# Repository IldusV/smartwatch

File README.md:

1. Download https://github.com/lvgl/lvgl library into the root directory of the smartwatch project
3. Add fb_tft display driver into linux kerner directory for GC9A01A  
4. Add CST816S touchscreen driver into the kernel directory
5. Configure Device Tree

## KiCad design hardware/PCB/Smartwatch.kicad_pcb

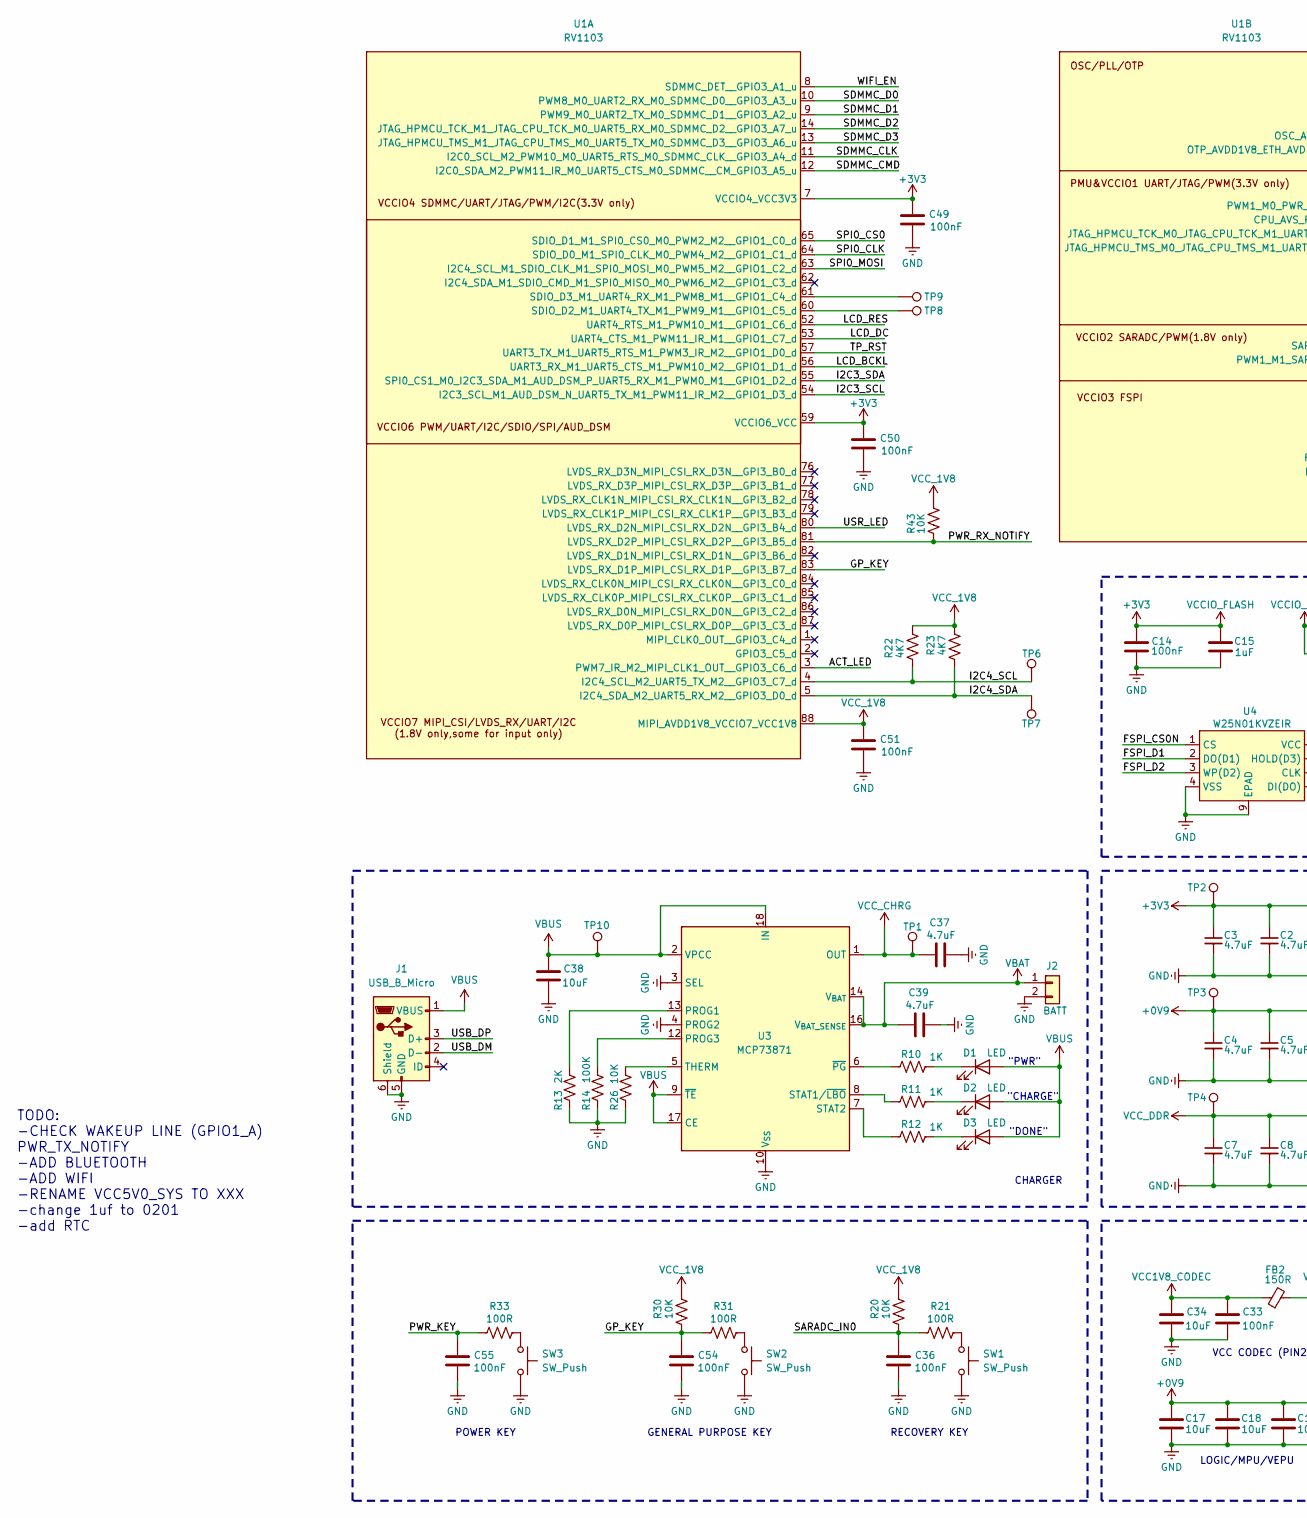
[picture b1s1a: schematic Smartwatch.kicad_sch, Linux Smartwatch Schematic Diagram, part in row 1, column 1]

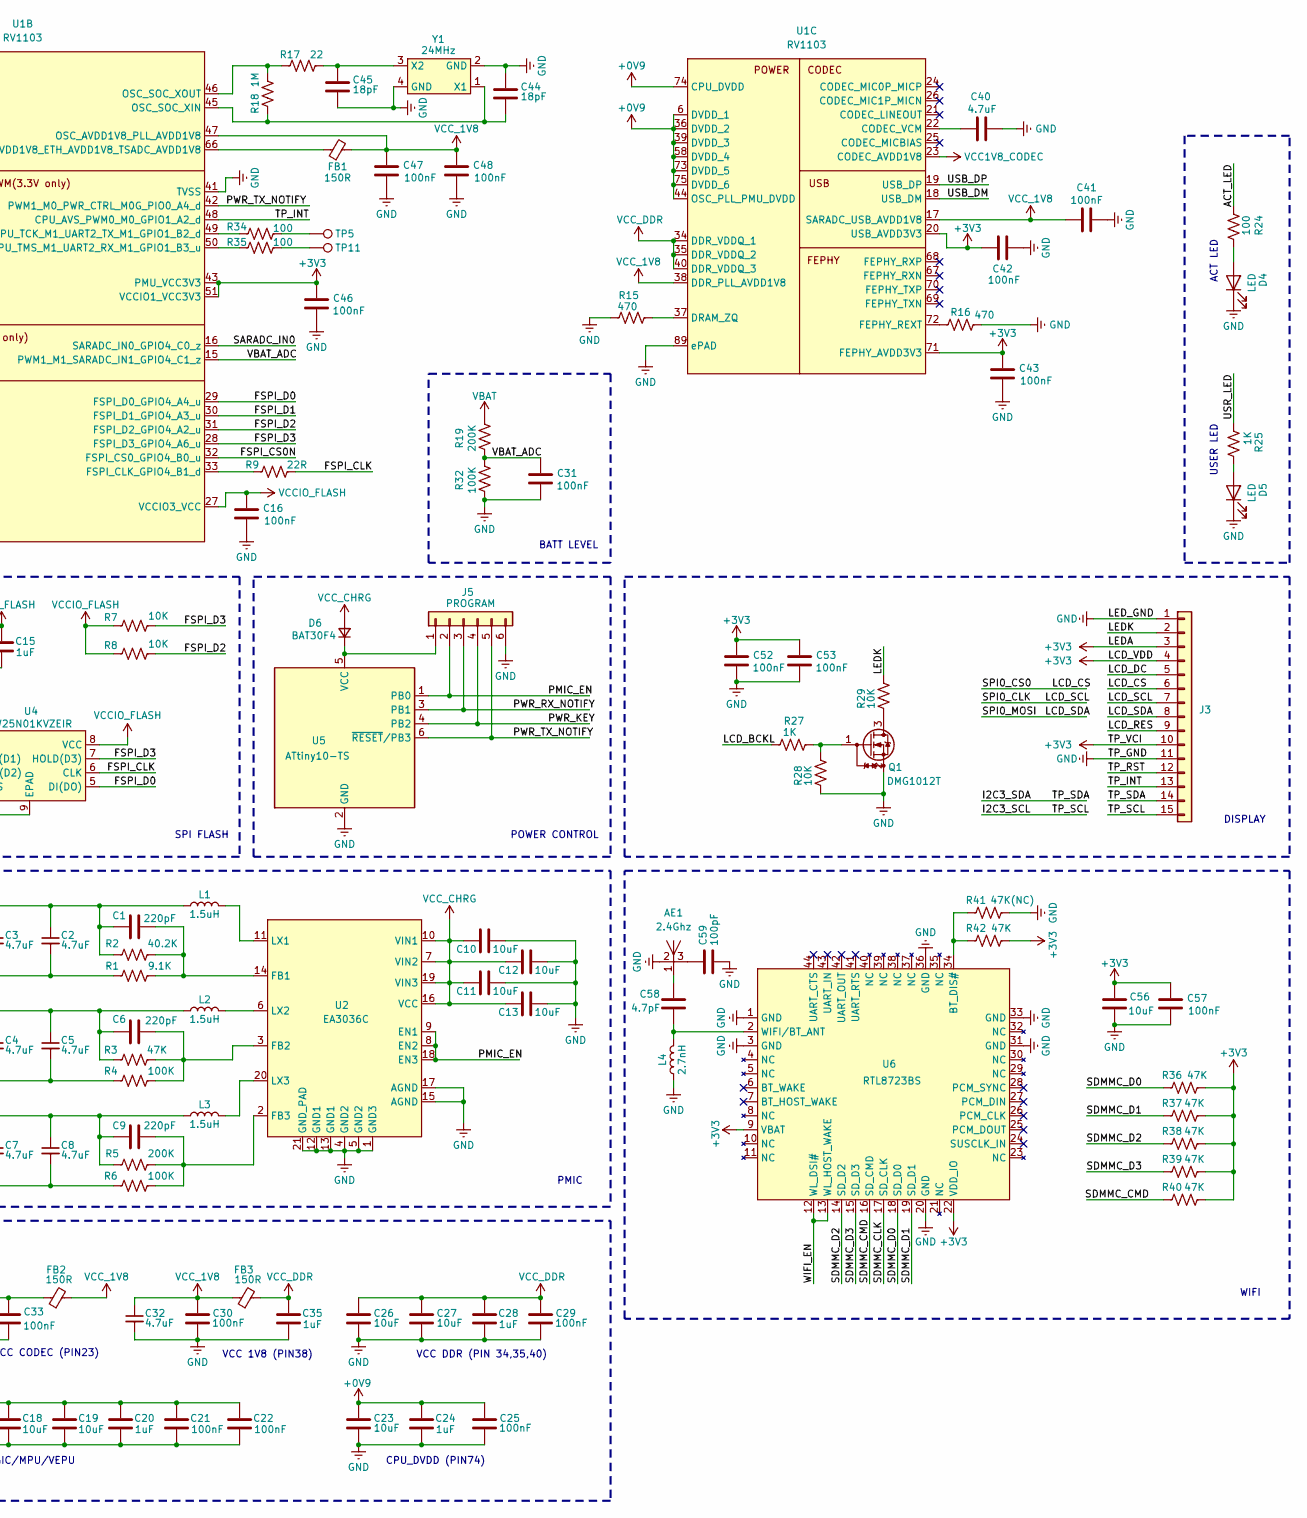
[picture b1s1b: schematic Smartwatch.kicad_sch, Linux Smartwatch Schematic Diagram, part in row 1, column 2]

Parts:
AE1: 2.4Ghz; 2.4Ghz_TE_Antenna
C1, C6, C9: 220pF; C_0201_0603Metric
C2, C3, C4, C5, C7, C8, C32, C37, C39, C40: 4.7uF; C_0201_0603Metric
C10, C11, C12, C13, C17, C18, C19, C23, C26, C27, C34, C38, C56: 10uF; C_0402_1005Metric
C14, C16, C21, C22, C25, C29, C30, C31, C33, C36, C41, C42, C43, C46, C47, C48, C49, C50, C51, C52, C53, C54, C55, C57: 100nF; C_0201_0603Metric
C15, C20, C24, C28, C35: 1uF; C_0201_0603Metric
C44, C45: 18pF; C_0201_0603Metric
C58: 4.7pF; C_0201_0603Metric
C59: 100pF; C_0201_0603Metric
D1, D2, D3, D4, D5: LED; LED_0201_0603Metric
D6: BAT30F4; D_0201_0603Metric
FB1, FB2, FB3: 150R; L_0402_1005Metric
J1: USB_B_Micro; USB_Micro-B_Molex_47346-0001
J2: BATT; JST_Aliexpress_KAN_shop_1x02-1MP_P0.80mm_Horizontal
J3: Conn_01x15; Amphenol_1x15-1MP_P0.5mm_Horizontal
J5: PROGRAM; pinpad6
L1, L2, L3: 1.5uH; L_1008_2520Metric
L4: 2.7nH; L_0402_1005Metric
Q1: DMG1012T; SOT-523
R1: 9.1K; R_0201_0603Metric
R2: 40.2K; R_0201_0603Metric
R3, R36, R37, R38, R39, R40, R42: 47K; R_0201_0603Metric
R4, R6, R14, R32: 100K; R_0201_0603Metric
R5, R19: 200K; R_0201_0603Metric
R7, R8, R20, R26, R28, R29, R30, R43: 10K; R_0201_0603Metric
R9: 22R; R_0201_0603Metric
R10, R11, R12, R25, R27: 1K; R_0201_0603Metric
R13: 2K; R_0201_0603Metric
R15, R16: 470; R_0201_0603Metric
R17: 22; R_0201_0603Metric
R18: 1M; R_0201_0603Metric
R21, R31, R33: 100R; R_0201_0603Metric
R22, R23: 4K7; R_0201_0603Metric
R24, R34, R35: 100; R_0201_0603Metric
R41: 47K(NC); R_0201_0603Metric
SW1, SW2, SW3: SW_Push; SW_1.8x4.5x3.5
TP1, TP2, TP3, TP4, TP5, TP6, TP7, TP8, TP9, TP10, TP11: TestPoint; TP
U1: RV1103; QFN-88_EP_9x9_Pitch0.35mm
U2: EA3036C; QFN-20-1EP_3x3mm_P0.4mm_EP1.65x1.65mm
U3: MCP73871; QFN-20-1EP_4x4mm_P0.5mm_EP2.5x2.5mm
U4: W25N01KVZEIR; WSON-8-1EP_8x6mm_P1.27mm_EP3.4x4.3mm
U5: ATtiny10-TS; SOT-23-6
U6: RTL8723BS; QFN-44_12.64x12.64_Pitch0.9mm
Y1: 24MHz; Crystal_SMD_2016-4Pin_2.0x1.6mm

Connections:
+0V9: C4.1, C5.1, C6.1, C17.1, C18.1, C19.1, C20.1, C21.2, C22.2, C23.1, C24.1, C25.2, L2.1, R3.1, TP3.1, U1.6 (DVDD_1), U1.36 (DVDD_2), U1.39 (DVDD_3), U1.44 (OSC_PLL_PMU_DVDD), U1.58 (DVDD_4), U1.73 (DVDD_5), U1.74 (CPU_DVDD), U1.75 (DVDD_6)
+3V3: C1.1, C2.1, C3.1, C14.2, C15.1, C16.2, C42.2, C43.2, C46.2, C49.2, C50.2, C52.2, C53.2, C56.1, C57.2, J3.3, J3.4, J3.10, L1.1, R2.1, R7.1, R8.1, R36.2, R37.2, R38.2, R39.2, R40.2, R42.2, TP2.1, U1.7 (VCCIO4_VCC3V3), U1.20 (USB_AVDD3V3), U1.27 (VCCIO3_VCC), U1.43 (PMU_VCC3V3), U1.51 (VCCIO1_VCC3V3), U1.59 (VCCIO6_VCC), U1.71 (FEPHY_AVDD3V3), U4.8 (VCC), U6.9 (VBAT), U6.22 (VDD_IO)
/ACT_LED: R24.1, U1.3 (PWM7_IR_M2_MIPI_CLK1_OUT__GPIO3_C6_d)
/FSPI_CLK: R9.2, U4.6 (CLK)
/FSPI_CS0N: U1.32 (FSPI_CS0_GPIO4_B0_u), U4.1 (CS)
/FSPI_D0: U1.29 (FSPI_D0_GPIO4_A4_u), U4.5 (DI(DO))
/FSPI_D1: U1.30 (FSPI_D1_GPIO4_A3_u), U4.2 (DO(D1))
/FSPI_D2: R8.2, U1.31 (FSPI_D2_GPIO4_A2_u), U4.3 (WP(D2))
/FSPI_D3: R7.2, U1.28 (FSPI_D3_GPIO4_A6_u), U4.7 (HOLD(D3))
/GP_KEY: C54.2, R30.1, R31.1, U1.83 (LVDS_RX_D1P_MIPI_CSI_RX_D1P__GPI3_B7_d)
/I2C3_SCL: J3.15, U1.54 (I2C3_SCL_M1_AUD_DSM_N_UART5_TX_M1_PWM11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)
/I2C3_SDA: J3.14, U1.55 (SPI0_CS1_M0_I2C3_SDA_M1_AUD_DSM_P_UART5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)
/I2C4_SCL: R22.1, TP6.1, U1.4 (I2C4_SCL_M2_UART5_TX_M2__GPIO3_C7_d)
/I2C4_SDA: R23.1, TP7.1, U1.5 (I2C4_SDA_M2_UART5_RX_M2__GPIO3_D0_d)
/LCD_BCKL: R27.1, U1.56 (UART3_RX_M1_UART5_CTS_M1_PWM10_M2__GPIO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)
/LCD_CS: J3.6, U1.65 (SDIO_D1_M1_SPI0_CS0_M0_PWM2_M2__GPIO1_C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)
/LCD_DC: J3.5, U1.53 (UART4_CTS_M1_PWM11_IR_M1__GPIO1_C7_d)
/LCD_RES: J3.9, U1.52 (UART4_RTS_M1_PWM10_M1__GPIO1_C6_d)
/LCD_SCL: J3.7, U1.64 (SDIO_D0_M1_SPI0_CLK_M0_PWM4_M2__GPIO1_C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)
/LCD_SDA: J3.8, U1.63 (I2C4_SCL_M1_SDIO_CLK_M1_SPI0_MOSI_M0_PW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)
/LEDK: J3.2, R29.2
/PMIC_EN: J5.2, U2.8 (EN2), U2.9 (EN1), U2.18 (EN3), U5.1 (PB0)
/PWR_KEY: C55.2, J5.4, R33.1, U5.4 (PB2)
/PWR_RX_NOTIFY: J5.3, R43.1, U1.81 (LVDS_RX_D2P_MIPI_CSI_RX_D2P__GPI3_B5_d), U5.3 (PB1)
/PWR_TX_NOTIFY: J5.5, U1.42 (PWM1_M0_PWR_CTRL_M0G_PIO0_A4_d), U5.6 (~RESET/PB3)
/SARADC_IN0: C36.2, R20.1, R21.1, U1.16 (SARADC_IN0_GPIO4_C0_z)
/SDMMC_CLK: U1.11 (I2C0_SCL_M2_PWM10_M0_UART5_RTS_M0_SDMMC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), U6.17 (SD_CLK)
/SDMMC_CMD: R40.1, U1.12 (I2C0_SDA_M2_PWM11_IR_M0_UART5_CTS_M0_SD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), U6.16 (SD_CMD)
/SDMMC_D0: R36.1, U1.10 (PWM8_M0_UART2_RX_M0_SDMMC_D0__GPIO3_A3_u), U6.18 (SD_D0)
/SDMMC_D1: R37.1, U1.9 (PWM9_M0_UART2_TX_M0_SDMMC_D1__GPIO3_A2_u), U6.19 (SD_D1)
/SDMMC_D2: R38.1, U1.14 (JTAG_HPMCU_TCK_M1_JTAG_CPU_TCK_M0_UART5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), U6.14 (SD_D2)
/SDMMC_D3: R39.1, U1.13 (JTAG_HPMCU_TMS_M1_JTAG_CPU_TMS_M0_UART5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), U6.15 (SD_D3)
/TP_INT: J3.13, U1.48 (CPU_AVS_PWM0_M0_GPIO1_A2_d)
/TP_RST: J3.12, U1.57 (UART3_TX_M1_UART5_RTS_M1_PWM3_IR_M2__GP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)
/USB_DM: J1.2 (D-), U1.18 (USB_DM)
/USB_DP: J1.3 (D+), U1.19 (USB_DP)
/USR_LED: R25.1, U1.80 (LVDS_RX_D2N_MIPI_CSI_RX_D2N__GPI3_B4_d)
/VBAT_ADC: C31.2, R19.1, R32.2, U1.15 (PWM1_M1_SARADC_IN1_GPIO4_C1_z)
/WIFI_EN: U1.8 (SDMMC_DET__GPIO3_A1_u), U6.12 (WL_DSI#), U6.13 (WL_HOST_WAKE)
GND: AE1.2, C2.2, C3.2, C4.2, C5.2, C7.2, C8.2, C10.1, C11.1, C12.1, C13.1, C14.1, C15.2, C16.1, C17.2, C18.2, C19.2, C20.2, C21.1, C22.1, C23.2, C24.2, C25.1, C26.2, C27.2, C28.2, C29.1, C30.1, C31.1, C32.2, C33.1, C34.2, C35.2, C36.1, C37.2, C38.2, C39.2, C40.2, C41.2, C42.1, C43.1, C44.2, C45.1, C46.1, C47.1, C48.1, C49.1, C50.1, C51.1, C52.1, C53.1, C54.1, C55.1, C56.2, C57.1, C59.2, D4.1 (K), D5.1 (K), J1.5 (GND), J1.6 (Shield), J2.2, J3.1, J3.11, J5.6, L4.1, Q1.2 (S), R1.1, R4.1, R6.1, R13.1, R14.1, R15.1, R16.2, R26.1, R28.1, R32.1, R41.2, SW1.2, SW2.2, SW3.2, U1.41 (TVSS), U1.89 (ePAD), U2.1 (GND3), U2.4 (GND2), U2.5 (GND2), U2.12 (GND1), U2.13 (GND1), U2.15 (AGND), U2.17 (AGND), U2.21 (GND_PAD), U3.3 (SEL), U3.4 (PROG2), U3.10 (V_{SS}), U3.11 (V_{SS}), U3.21 (V_{SS}), U4.4 (VSS), U4.9 (EPAD), U5.2 (GND), U6.1 (GND), U6.3 (GND), U6.20 (GND), U6.31 (GND), U6.33 (GND), U6.36 (GND), Y1.2 (GND), Y1.4 (GND)
unnamed: AE1.1, C58.2
unnamed: AE1.3, C59.1
unnamed: D1.1 (K), R10.2
unnamed: D2.1 (K), R11.2
unnamed: D3.1 (K), R12.2
unnamed: D4.2 (A), R24.2
unnamed: D5.2 (A), R25.2
unnamed: D6.1 (K), J5.1, U5.5 (VCC)
unnamed: Q1.3 (D), R29.1
unnamed: Q1.1 (G), R27.2, R28.2
unnamed: R21.2, SW1.1
unnamed: R31.2, SW2.1
unnamed: R33.2, SW3.1
unnamed: R34.2, TP5.1
unnamed: R35.2, TP11.1
unnamed: TP8.1, U1.60 (SDIO_D2_M1_UART4_TX_M1_PWM9_M1__GPIO1_C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)
unnamed: TP9.1, U1.61 (SDIO_D3_M1_UART4_RX_M1_PWM8_M1__GPIO1_C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)
unnamed: R9.1, U1.33 (FSPI_CLK_GPIO4_B1_d)
unnamed: R34.1, U1.49 (JTAG_HPMCU_TCK_M0_JTAG_CPU_TCK_M1_UART2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)
unnamed: R35.1, U1.50 (JTAG_HPMCU_TMS_M0_JTAG_CPU_TMS_M1_UART2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)
unnamed: C44.1, R18.1, U1.45 (OSC_SOC_XIN), Y1.1 (X1)
unnamed: R17.1, R18.2, U1.46 (OSC_SOC_XOUT)
unnamed: FB1.1, U1.66 (OTP_AVDD1V8_ETH_AVDD1V8_TSADC_AVDD1V8)
unnamed: C40.1, U1.22 (CODEC_VCM)
unnamed: R15.2, U1.37 (DRAM_ZQ)
unnamed: R16.1, U1.72 (FEPHY_REXT)
unnamed: C1.2, R1.2, R2.2, U2.14 (FB1)
unnamed: C6.2, R3.2, R4.2, U2.3 (FB2)
unnamed: C9.2, R5.2, R6.2, U2.2 (FB3)
unnamed: L1.2, U2.11 (LX1)
unnamed: L2.2, U2.6 (LX2)
unnamed: L3.2, U2.20 (LX3)
unnamed: R13.2, U3.13 (PROG1)
unnamed: R14.2, U3.12 (PROG3)
unnamed: R11.1, U3.8 (STAT1/~LBO)
unnamed: R12.1, U3.7 (STAT2)
unnamed: R26.2, U3.5 (THERM)
unnamed: R10.1, U3.6 (~PG)
unnamed: R41.1, R42.1, U6.34 (BT_DIS#)
unnamed: C58.1, L4.2, U6.2 (WIFI/BT_ANT)
unnamed: C45.2, R17.2, Y1.3 (X2)
VBAT: C39.1, J2.1, R19.2, U3.14 (V_{BAT}), U3.15 (V_{BAT}), U3.16 (V_{BAT_SENSE})
VBUS: C38.1, D1.2 (A), D2.2 (A), D3.2 (A), J1.1 (VBUS), TP10.1, U3.2 (VPCC), U3.9 (~TE), U3.17 (CE), U3.18 (IN), U3.19 (IN)
VCC1V8_CODEC: C33.2, C34.1, FB2.1, U1.23 (CODEC_AVDD1V8)
VCC_1V8: C30.2, C32.1, C41.1, C47.2, C48.2, C51.2, FB1.2, FB2.2, FB3.1, R20.2, R22.2, R23.2, R30.2, R43.2, U1.17 (SARADC_USB_AVDD1V8), U1.38 (DDR_PLL_AVDD1V8), U1.47 (OSC_AVDD1V8_PLL_AVDD1V8), U1.88 (MIPI_AVDD1V8_VCCIO7_VCC1V8)
VCC_CHRG: C10.2, C11.2, C12.2, C13.2, C37.1, D6.2 (A), TP1.1, U2.7 (VIN2), U2.10 (VIN1), U2.16 (VCC), U2.19 (VIN3), U3.1 (OUT), U3.20 (OUT)
VCC_DDR: C7.1, C8.1, C9.1, C26.1, C27.1, C28.1, C29.2, C35.1, FB3.2, L3.1, R5.1, TP4.1, U1.34 (DDR_VDDQ_1), U1.35 (DDR_VDDQ_2), U1.40 (DDR_VDDQ_3)

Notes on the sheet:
"DONE"
POWER CONTROL
LOGIC/MPU/VEPU
ACT LED
"PWR"
GENERAL PURPOSE KEY
CPU_DVDD (PIN74)
VCC CODEC (PIN23)
"CHARGE"
RECOVERY KEY
WIFI
CHARGER
SPI FLASH
BATT LEVEL
DISPLAY
USER LED
VCC DDR (PIN 34,35,40)
PMIC
TODO: -CHECK WAKEUP LINE (GPIO1_A) PWR_TX_NOTIFY -ADD BLUETOOTH -ADD WIFI -RENAME VCC5V0_SYS TO XXX -change 1uf to 0201 -add RTC
VCC 1V8 (PIN38)
POWER KEY

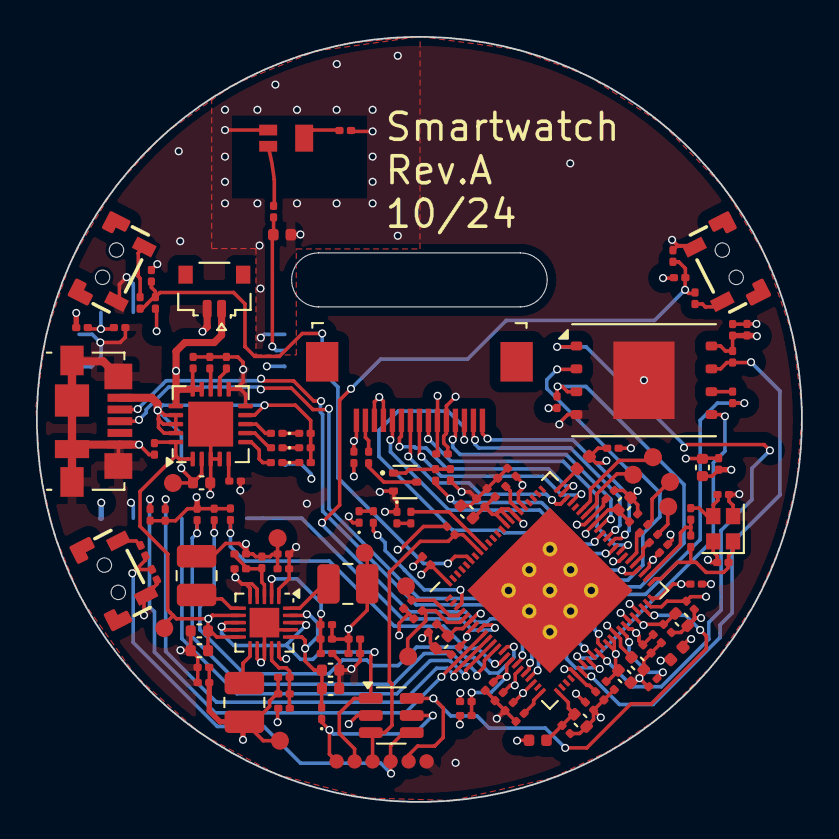
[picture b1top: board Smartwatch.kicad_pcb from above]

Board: 4 copper layers, 42.5 x 42.5 mm, 142 parts (1 on the bottom side), 87 nets.

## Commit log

2024-05-26 initial
2024-05-26 added Makefile
2024-05-27 added more files
2024-06-17 ui files generated by sqline studio
2024-06-17 needles sync with sytem time
2024-06-17 updated ui to 8.3.11
2024-06-17 fix clock
2024-06-22 added os_drv
2024-10-13 PCB rev.A completed
2024-10-13 PCB rev.A ordered
2024-10-13 Added Smartwatch_rev.A.pdf
2024-12-27 PCB rev.B completed
2024-12-27 Remove redundant PDF
